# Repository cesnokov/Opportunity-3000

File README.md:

Opportunity-3000
=======

LED Matrix Display with Keyboard.
Under Construction!!!

Project Parts
------------

- [NeoMatrix Generator](https://github.com/cesnokov/NeoMatrix-Generator)

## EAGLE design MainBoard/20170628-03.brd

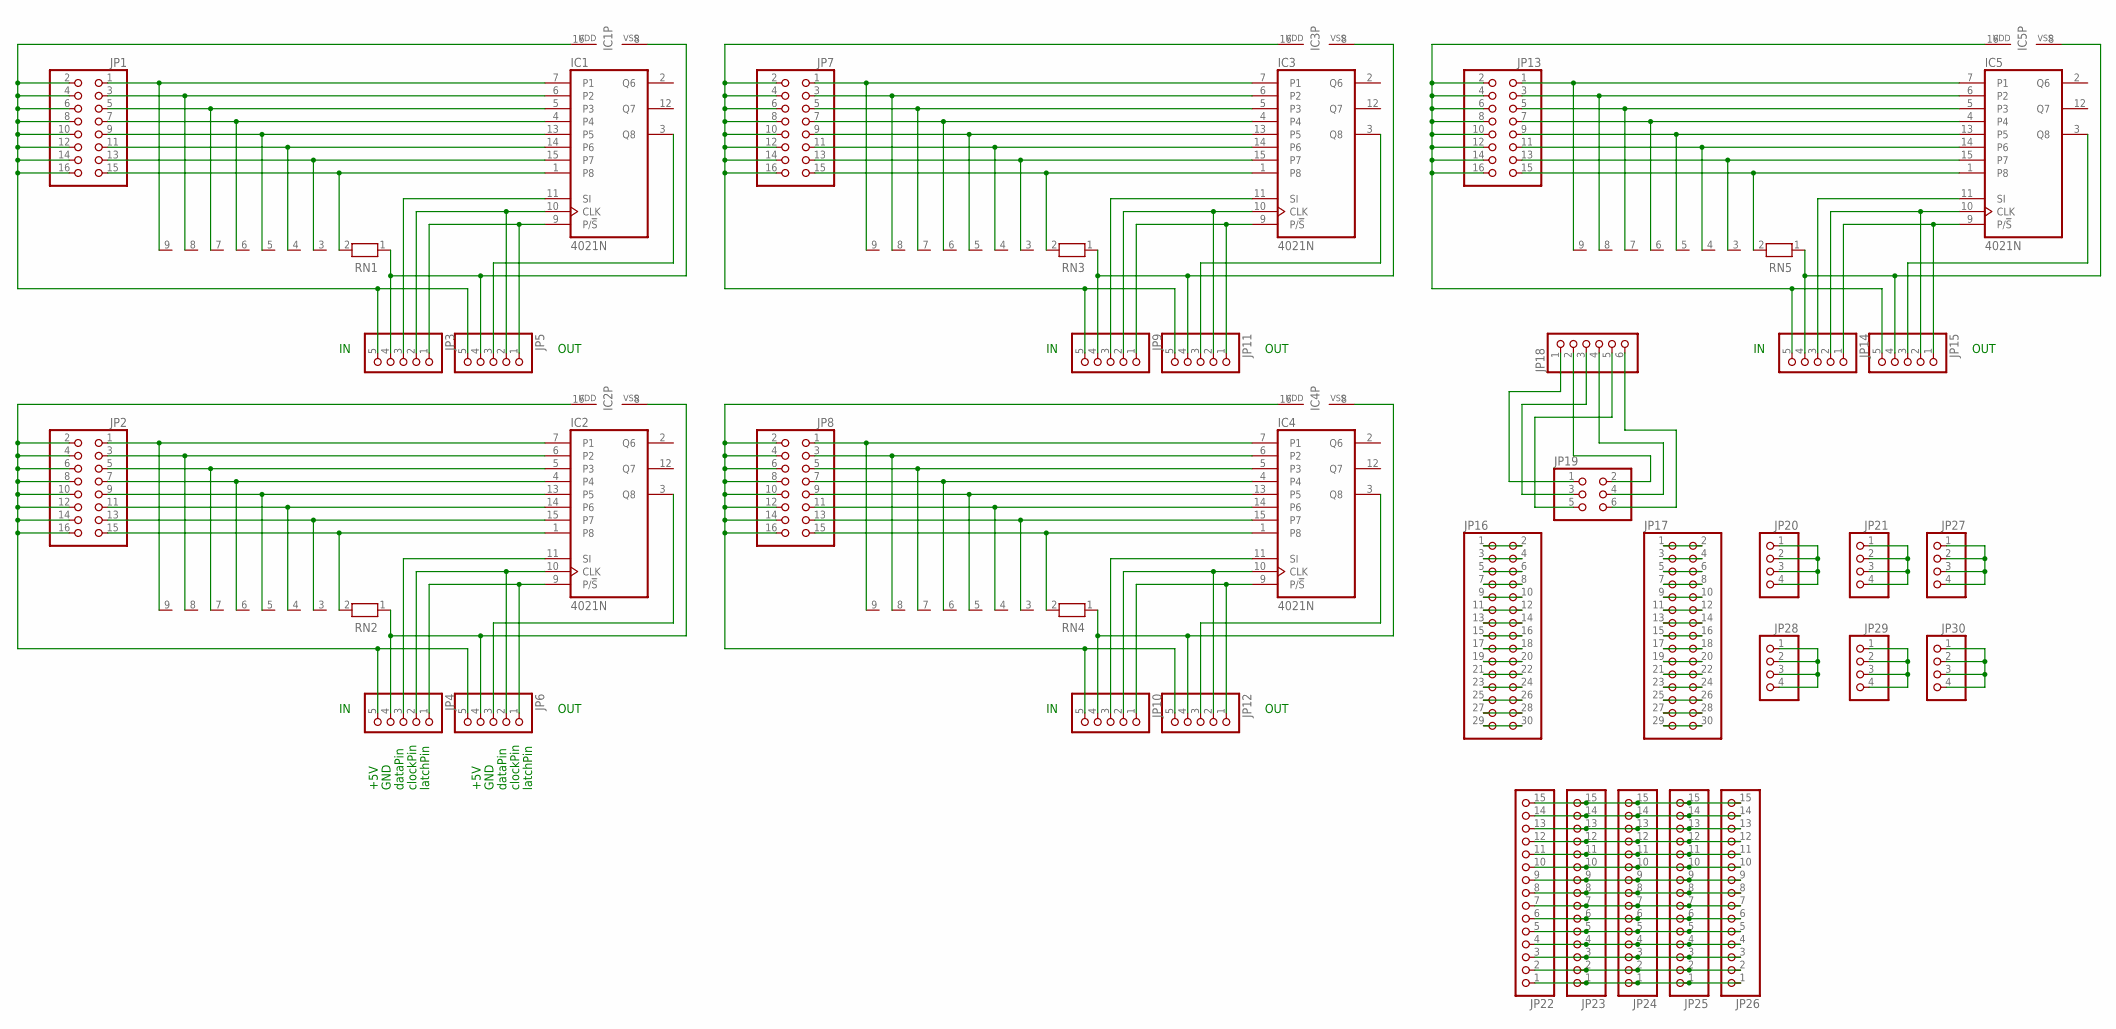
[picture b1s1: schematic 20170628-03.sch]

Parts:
IC1, IC2, IC3, IC4, IC5: 4021N; DIL16
JP1, JP2, JP7, JP8, JP13: PINHD-2X8; 2X08
JP3, JP4, JP5, JP6, JP9, JP10, JP11, JP12, JP14, JP15: PINHD-1X5; 1X05
JP16, JP17: PINHD-2X15; 2X15
JP18: PINHD-1X6; 1X06
JP19: PINHD-2X3; 2X03
JP20, JP21, JP27, JP28, JP29, JP30: PINHD-1X4; 1X04
JP22, JP23, JP24, JP25, JP26: PINHD-1X15; 1X15
RN1, RN2, RN3, RN4, RN5: RN08; RN-9

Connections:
unnamed: IC2.7 (P1), JP2.1, RN2.9
unnamed: IC2.6 (P2), JP2.3, RN2.8
unnamed: IC2.5 (P3), JP2.5, RN2.7
unnamed: IC2.4, JP2.7, RN2.6
unnamed: IC2.13 (P5), JP2.9, RN2.5
unnamed: IC2.14 (P6), JP2.11, RN2.4
unnamed: IC2.15 (P7), JP2.13, RN2.3
unnamed: IC2.1 (P8), JP2.15, RN2.2
unnamed: IC2.9 (P/!S), JP4.1, JP6.1
unnamed: IC2.10 (CLK), JP4.2, JP6.2
unnamed: IC2.3 (Q8), JP6.3
unnamed: IC2.16 (VDD), JP2.2, JP2.4, JP2.6, JP2.8, JP2.10, JP2.12, JP2.14, JP2.16, JP4.5, JP6.5
unnamed: IC2.8 (VSS), JP4.4, JP6.4, RN2.1
unnamed: IC1.7 (P1), JP1.1, RN1.9
unnamed: IC1.6 (P2), JP1.3, RN1.8
unnamed: IC1.5 (P3), JP1.5, RN1.7
unnamed: IC1.4, JP1.7, RN1.6
unnamed: IC1.13 (P5), JP1.9, RN1.5
unnamed: IC1.15 (P7), JP1.13, RN1.3
unnamed: IC1.11 (SI), JP3.3
unnamed: IC1.14 (P6), JP1.11, RN1.4
unnamed: IC1.1 (P8), JP1.15, RN1.2
unnamed: IC1.9 (P/!S), JP3.1, JP5.1
unnamed: IC1.10 (CLK), JP3.2, JP5.2
unnamed: IC1.3 (Q8), JP5.3
unnamed: IC1.16 (VDD), JP1.2, JP1.4, JP1.6, JP1.8, JP1.10, JP1.12, JP1.14, JP1.16, JP3.5, JP5.5
unnamed: IC1.8 (VSS), JP3.4, JP5.4, RN1.1
unnamed: IC3.7 (P1), JP7.1, RN3.9
unnamed: IC3.6 (P2), JP7.3, RN3.8
unnamed: IC3.5 (P3), JP7.5, RN3.7
unnamed: IC3.4, JP7.7, RN3.6
unnamed: IC3.13 (P5), JP7.9, RN3.5
unnamed: IC3.15 (P7), JP7.13, RN3.3
unnamed: IC3.11 (SI), JP9.3
unnamed: IC3.14 (P6), JP7.11, RN3.4
unnamed: IC3.1 (P8), JP7.15, RN3.2
unnamed: IC3.9 (P/!S), JP9.1, JP11.1
unnamed: IC3.10 (CLK), JP9.2, JP11.2
unnamed: IC3.3 (Q8), JP11.3
unnamed: IC3.16 (VDD), JP7.2, JP7.4, JP7.6, JP7.8, JP7.10, JP7.12, JP7.14, JP7.16, JP9.5, JP11.5
unnamed: IC3.8 (VSS), JP9.4, JP11.4, RN3.1
unnamed: IC2.11 (SI), JP4.3
unnamed: IC4.7 (P1), JP8.1, RN4.9
unnamed: IC4.6 (P2), JP8.3, RN4.8
unnamed: IC4.5 (P3), JP8.5, RN4.7
unnamed: IC4.4, JP8.7, RN4.6
unnamed: IC4.13 (P5), JP8.9, RN4.5
unnamed: IC4.15 (P7), JP8.13, RN4.3
unnamed: IC4.11 (SI), JP10.3
unnamed: IC4.14 (P6), JP8.11, RN4.4
unnamed: IC4.1 (P8), JP8.15, RN4.2
unnamed: IC4.9 (P/!S), JP10.1, JP12.1
unnamed: IC4.10 (CLK), JP10.2, JP12.2
unnamed: IC4.3 (Q8), JP12.3
unnamed: IC4.16 (VDD), JP8.2, JP8.4, JP8.6, JP8.8, JP8.10, JP8.12, JP8.14, JP8.16, JP10.5, JP12.5
unnamed: IC4.8 (VSS), JP10.4, JP12.4, RN4.1
unnamed: IC5.7 (P1), JP13.1, RN5.9
unnamed: IC5.6 (P2), JP13.3, RN5.8
unnamed: IC5.5 (P3), JP13.5, RN5.7
unnamed: IC5.4, JP13.7, RN5.6
unnamed: IC5.13 (P5), JP13.9, RN5.5
unnamed: IC5.15 (P7), JP13.13, RN5.3
unnamed: IC5.11 (SI), JP14.3
unnamed: IC5.14 (P6), JP13.11, RN5.4
unnamed: IC5.1 (P8), JP13.15, RN5.2
unnamed: IC5.9 (P/!S), JP14.1, JP15.1
unnamed: IC5.10 (CLK), JP14.2, JP15.2
unnamed: IC5.3 (Q8), JP15.3
unnamed: IC5.16 (VDD), JP13.2, JP13.4, JP13.6, JP13.8, JP13.10, JP13.12, JP13.14, JP13.16, JP14.5, JP15.5
unnamed: IC5.8 (VSS), JP14.4, JP15.4, RN5.1
unnamed: JP16.1, JP16.2
unnamed: JP16.3, JP16.4
unnamed: JP16.5, JP16.6
unnamed: JP16.7, JP16.8
unnamed: JP16.9, JP16.10
unnamed: JP16.11, JP16.12
unnamed: JP16.13, JP16.14
unnamed: JP16.15, JP16.16
unnamed: JP16.17, JP16.18
unnamed: JP16.19, JP16.20
unnamed: JP16.21, JP16.22
unnamed: JP16.23, JP16.24
unnamed: JP16.25, JP16.26
unnamed: JP16.27, JP16.28
unnamed: JP16.29, JP16.30
unnamed: JP17.1, JP17.2
unnamed: JP17.3, JP17.4
unnamed: JP17.5, JP17.6
unnamed: JP17.7, JP17.8
unnamed: JP17.9, JP17.10
unnamed: JP17.11, JP17.12
unnamed: JP17.13, JP17.14
unnamed: JP17.15, JP17.16
unnamed: JP17.17, JP17.18
unnamed: JP17.19, JP17.20
unnamed: JP17.21, JP17.22
unnamed: JP17.23, JP17.24
unnamed: JP17.25, JP17.26
unnamed: JP17.27, JP17.28
unnamed: JP17.29, JP17.30
unnamed: JP18.1, JP19.1
unnamed: JP18.3, JP19.3
unnamed: JP18.5, JP19.5
unnamed: JP18.2, JP19.2
unnamed: JP18.4, JP19.4
unnamed: JP18.6, JP19.6
unnamed: JP20.1, JP20.2, JP20.3, JP20.4
unnamed: JP21.1, JP21.2, JP21.3, JP21.4
unnamed: JP27.1, JP27.2, JP27.3, JP27.4
unnamed: JP22.1, JP23.1, JP24.1, JP25.1, JP26.1
unnamed: JP22.2, JP23.2, JP24.2, JP25.2, JP26.2
unnamed: JP22.3, JP23.3, JP24.3, JP25.3, JP26.3
unnamed: JP22.4, JP23.4, JP24.4, JP25.4, JP26.4
unnamed: JP22.5, JP23.5, JP24.5, JP25.5, JP26.5
unnamed: JP22.6, JP23.6, JP24.6, JP25.6, JP26.6
unnamed: JP22.7, JP23.7, JP24.7, JP25.7, JP26.7
unnamed: JP22.8, JP23.8, JP24.8, JP25.8, JP26.8
unnamed: JP22.9, JP23.9, JP24.9, JP25.9, JP26.9
unnamed: JP22.10, JP23.10, JP24.10, JP25.10, JP26.10
unnamed: JP22.11, JP23.11, JP24.11, JP25.11, JP26.11
unnamed: JP22.12, JP23.12, JP24.12, JP25.12, JP26.12
unnamed: JP22.13, JP23.13, JP24.13, JP25.13, JP26.13
unnamed: JP22.14, JP23.14, JP24.14, JP25.14, JP26.14
unnamed: JP22.15, JP23.15, JP24.15, JP25.15, JP26.15
unnamed: JP28.1, JP28.2, JP28.3, JP28.4
unnamed: JP29.1, JP29.2, JP29.3, JP29.4
unnamed: JP30.1, JP30.2, JP30.3, JP30.4

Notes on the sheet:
dataPin
latchPin
clockPin
GND
OUT
+5V

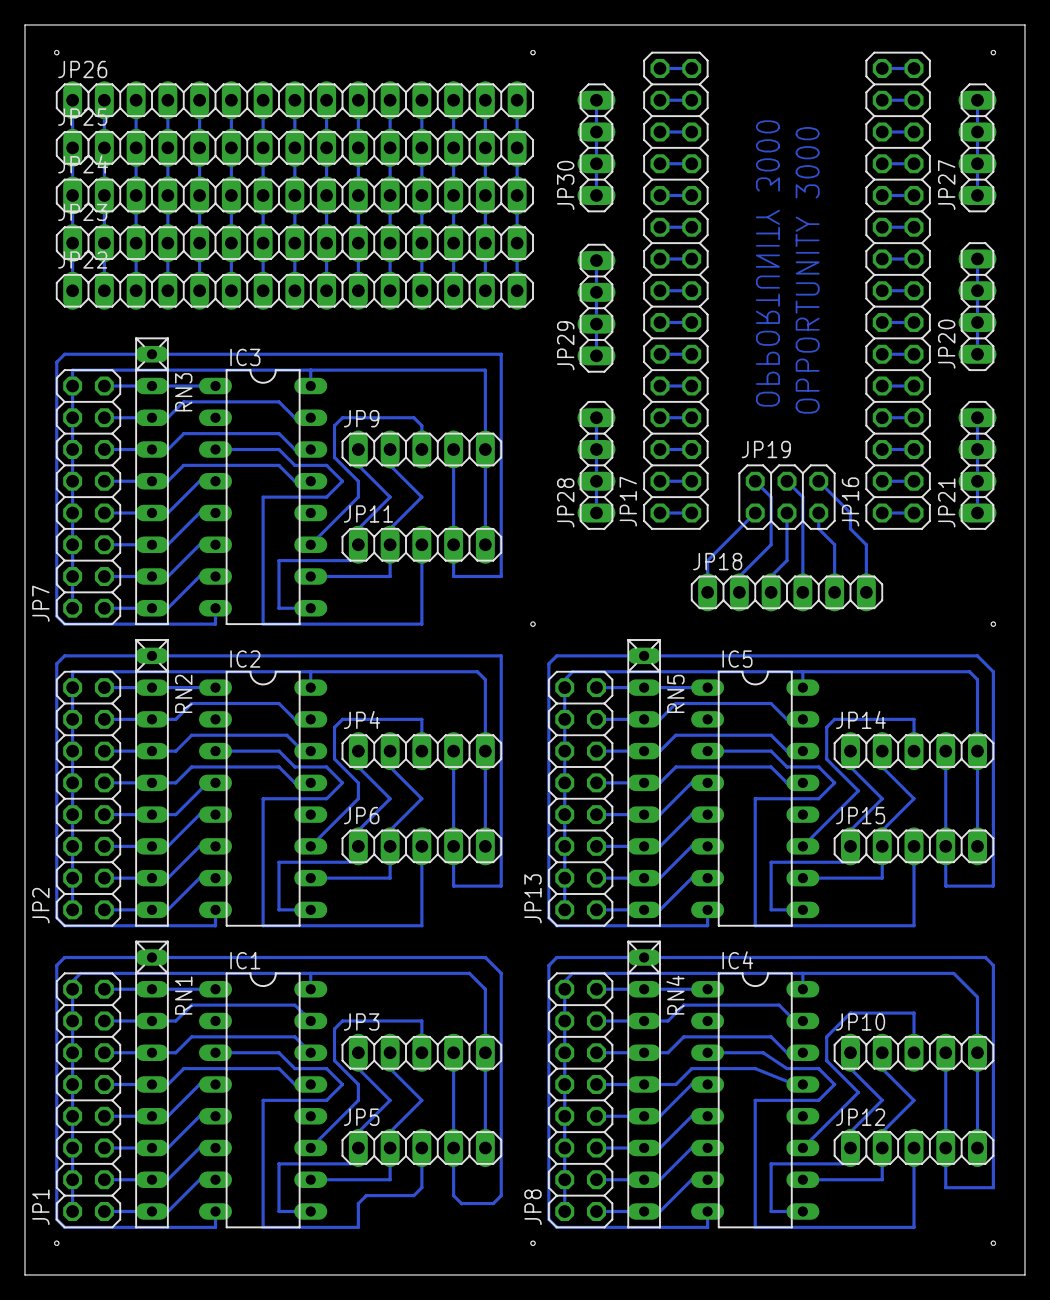
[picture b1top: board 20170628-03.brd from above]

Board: 2 copper layers, 80.0 x 100.0 mm, 40 parts (0 on the bottom side), 127 nets.
